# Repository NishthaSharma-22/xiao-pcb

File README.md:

## tiny gamepad

### what it does
- acts like a basic HID gamepad
- 4 buttons (wasd layout) + 4 leds that light up on button presses
- can be used to move in any game that accepts controller input

### components used:
- xiao rp2040
- 4x resistors
- 4x regular leds, nothing fancy
- 4x cherry mx switches
- designed in KiCad 

## the schematic:

## the pcb:

### to use:
download the gerber files from <code>prod.zip</code> if you want to get this pcb fabricated.

### i learned:
- pcb design for the first time + using KiCad
- writing firmware using <code>Adafruit_TinyUSB</code> to emulate a gamepad
- random stuff about some electronic components

### why i made this
i just wanted to make something physical for once - this project is really basic, but i loved making + learning about hardware, and now i want to make more stuff that clicks and lights up

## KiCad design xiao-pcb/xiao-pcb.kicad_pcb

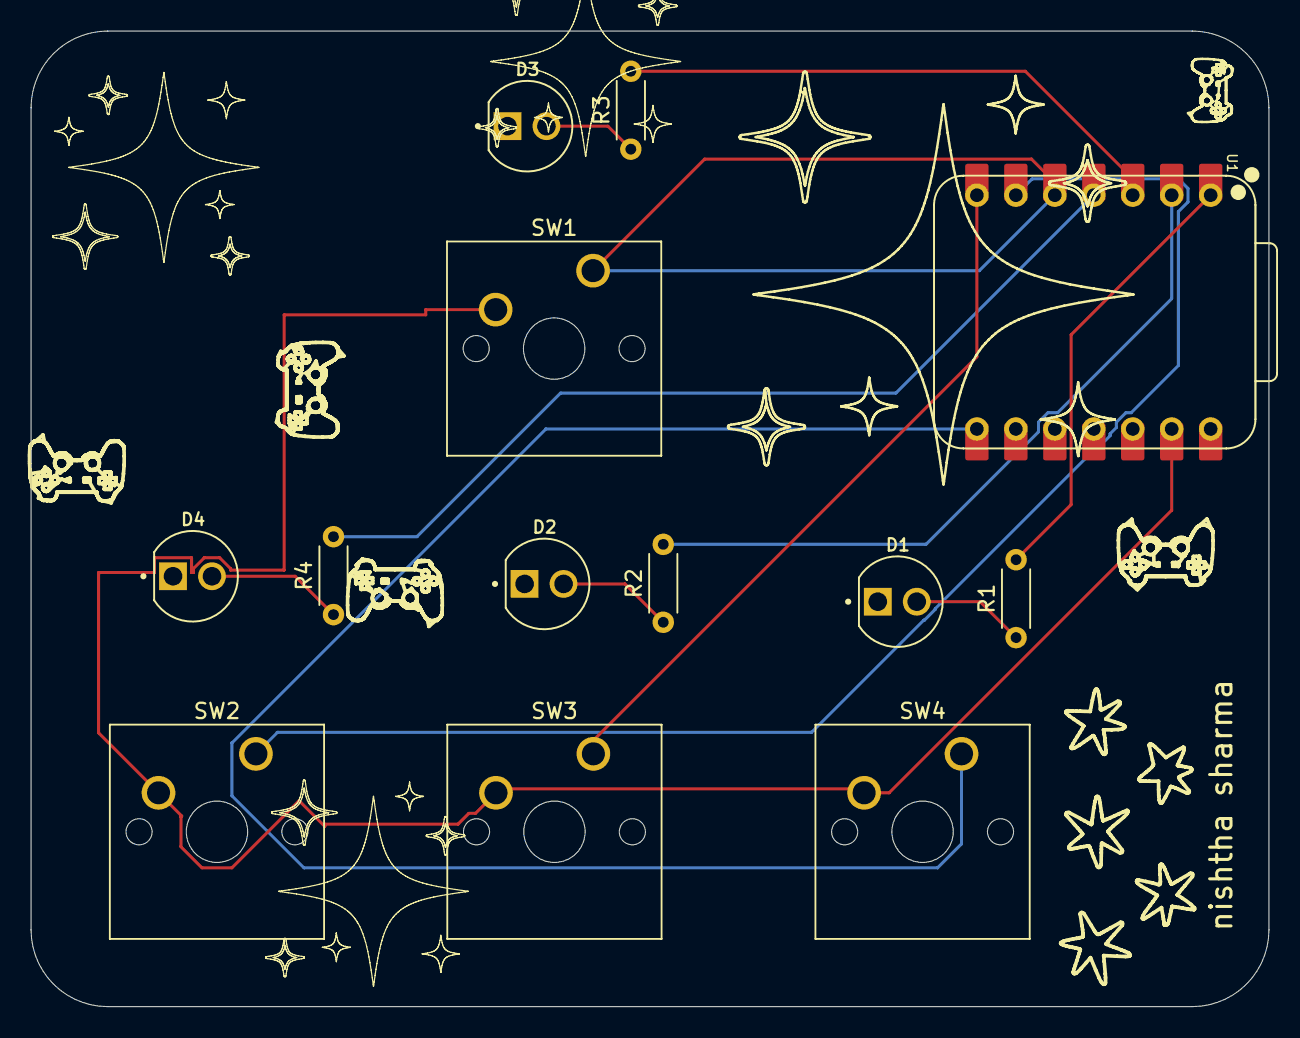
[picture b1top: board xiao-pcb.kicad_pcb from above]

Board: 2 copper layers, 80.7 x 63.6 mm, 13 parts (0 on the bottom side), 13 nets.

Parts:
D1, D2, D3, D4: L08R5000Q1; LEDRD254W57D500H1070
R1, R2, R3, R4: R; R_Axial_DIN0204_L3.6mm_D1.6mm_P5.08mm_Horizontal
SW1, SW2, SW3, SW4: SW_Push; SW_Cherry_MX_1.00u_PCB
U1: XIAO-RP2040-DIP

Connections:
GND: SW1.2, SW2.2, SW3.2, SW4.2, U1.13 (GND)
unnamed: D1.A, R1.1
unnamed: D2.A, R2.1
unnamed: D3.A, R3.1
unnamed: D4.A, R4.1
led1: R1.2, U1.1 (GPIO26/ADC0/A0)
led2: R2.2, U1.2 (GPIO27/ADC1/A1)
led3: R3.2, U1.3 (GPIO28/ADC2/A2)
led4: R4.2, U1.4 (GPIO29/ADC3/A3)
s1: SW1.1, U1.5 (GPIO6/SDA)
sw2: SW2.1, U1.6 (GPIO7/SCL)
sw3: SW3.1, U1.7 (GPIO0/TX)
sw4: SW4.1, U1.8 (GPIO1/RX)

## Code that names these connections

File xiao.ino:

#include "Adafruit_TinyUSB.h"

int btn1 = 1;
int btn2 = 2;
int btn3 = 3;
int btn4 = 4;

int led1 = 5;
int led2 = 6;
int led3 = 7;
int led4 = 8;

Adafruit_USBD_Gamepad gamepad;

void setup(){
    pinMode(btn1, INPUT_PULLUP);
    pinMode(btn2, INPUT_PULLUP);
    pinMode(btn3, INPUT_PULLUP);
    pinMode(btn4, INPUT_PULLUP);


    pinMode(led1, OUTPUT);
    pinMode(led2, OUTPUT);
    pinMode(led3, OUTPUT);
    pinMode(led4, OUTPUT);

    digitalWrite(led1, LOW);
    digitalWrite(led2, LOW);
    digitalWrite(led3, LOW);
    digitalWrite(led4, LOW);

    gamepad.begin();

}

void loop(){
    bool pressed1 = !digitalRead(btn1);
    bool pressed2 = !digitalRead(btn2);
    bool pressed3 = !digitalRead(btn3);
    bool pressed4 = !digitalRead(btn4);
    digitalWrite(led1, pressed1 ? HIGH :LOW);
    digitalWrite(led2, pressed2 ? HIGH: LOW);
    digitalWrite(led3, pressed3 ? HIGH: LOW);
    digitalWrite(led4, pressed4 ? HIGH: LOW);

    if (pressed1) gamepad.press(1);
    else gamepad.release(1);

    if (pressed2) gamepad.press(2);
    else gamepad.release(2);

    if (pressed3) gamepad.press(3);
    else gamepad.release(3);

    if (pressed4) gamepad.press(4);
    else gamepad.release(4);

    delay(10);

}

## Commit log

2025-07-17 pcb updates
2025-07-18 added gerbers
2025-07-18 firmware
